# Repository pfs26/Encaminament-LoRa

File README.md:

# LoRa Static Routing Protocol for Monitoring Applications
This work presents the design and implementation of a modular and layered communication protocol based on LoRa and static routing, intended for monitoring device networks in extensive or isolated environments, where human presence is limited. The goal is to reduce the dependency on LoRaWAN gateways, taking advantage of the fact that devices are usually static and allow the use of predefined communication routes.

An application optimized for linear networks -a topology particularly useful in railway lines or tunnels- has been developed based on this protocol. It focuses on minimizing the energy consumption of the devices through a synchronization strategy between nodes, which allows coordinating transmissions and reducing the active time of the devices, without compromising reliability or the routing mechanisms provided by the protocol. The conducted tests have demonstrated that the proposed solution is viable, scalable, and efficient in environments where energy consumption and coverage are critical.

## Features
- **Custom LoRa MAC Protocol**
  - Layered protocol structure for modularity and easy extension
  - Unique node addressing and message relay
  - Static routing using **precomputed** routing tables, configurable during runtime
  - **CSMA** to avoid collisions, combined with **Binary Exponential Backoff (BEB)** if channel activity is detected
  - **Adaptive retransmission**, with dynamic transmission power adjustment
  - **TTL mechanism** to prevent routing loops
  - Simple **checksum-based error detection**
  - **Message deduplication** at the transport layer
  - **End-to-end acknowledgments** for reliable message delivery
  
- **LoRaWAN Relaying**
  - Nodes with LoRaWAN access can relay packets to the gateway
  - Handles end-to-end acknowledgment since LoRaWAN gateways cannot do this natively

- **Transport Layer**
  - Allows for optional end-to-end reliability
  - Segment deduplication 

- **Application Layer**
  - User-defined and fully customizable
  - Includes built-in low-power management, to be run on port `0x01`
  - Supports any logic needed, such as I2C sensor communication, dynamic configuration, etc.

## Repository Structure
```
├── firmware/          # ESP32 firmware for LoRa node
│   ├── src/           # LoRa protocol implementation
│   ├── include/       # Header files
│   ├── config/        # LoRa settings
├── tests/             # Tests and results, done during validation
├── memoria/           # Design and code documentation (.tex format)
└── README.md          # This file
```

## Protocol Architecture
The protocol is structured into multiple layers, each handling specific aspects of communication:

### LoRa Physical Layer
- Uses **SX1262 transceivers**
- Configurable modulation settings (SF, BW, TX power)

### MAC Layer
- **CSMA** with **Listen Before Talk (LBT)** to reduce collisions
- **Binary Exponential Backoff (BEB)** if the channel is busy

### Routing Layer
- **Static routing with runtime updates** via API (`RoutingTable_*()` functions)
- **TTL enforcement** to prevent looping packets
- Multiple LoRa interfaces support, for different configurations (raw LoRa vs LoRaWAN, or multiple raw LoRa transceivers)

### LoRaWAN Support
- Nodes with LoRaWAN access can forward packets to the gateway
- Uses LoRaWAN v1.1, using non-volatile storage to store nonces and keys
- OTAA for enhanced security
- Automatic LoRaWAN and raw LoRa mode swapping, storing connection information to avoid OTAA reactivations for each transmission 

### Transport Layer
- **Segment deduplication** using a unique **Segment ID**
- **End-to-end acknowledgment** ensures reliable delivery
- Automatic retransmissions if no acknowledgment is recevied, applying an exponential backoff after each attempt
- Unrealiable segments for quick end-to-end messaging

### Application Layer
- Customisable by the user, depending on requirements
- Uses the full protocol stack underneath
- **Built-in low-power** management application

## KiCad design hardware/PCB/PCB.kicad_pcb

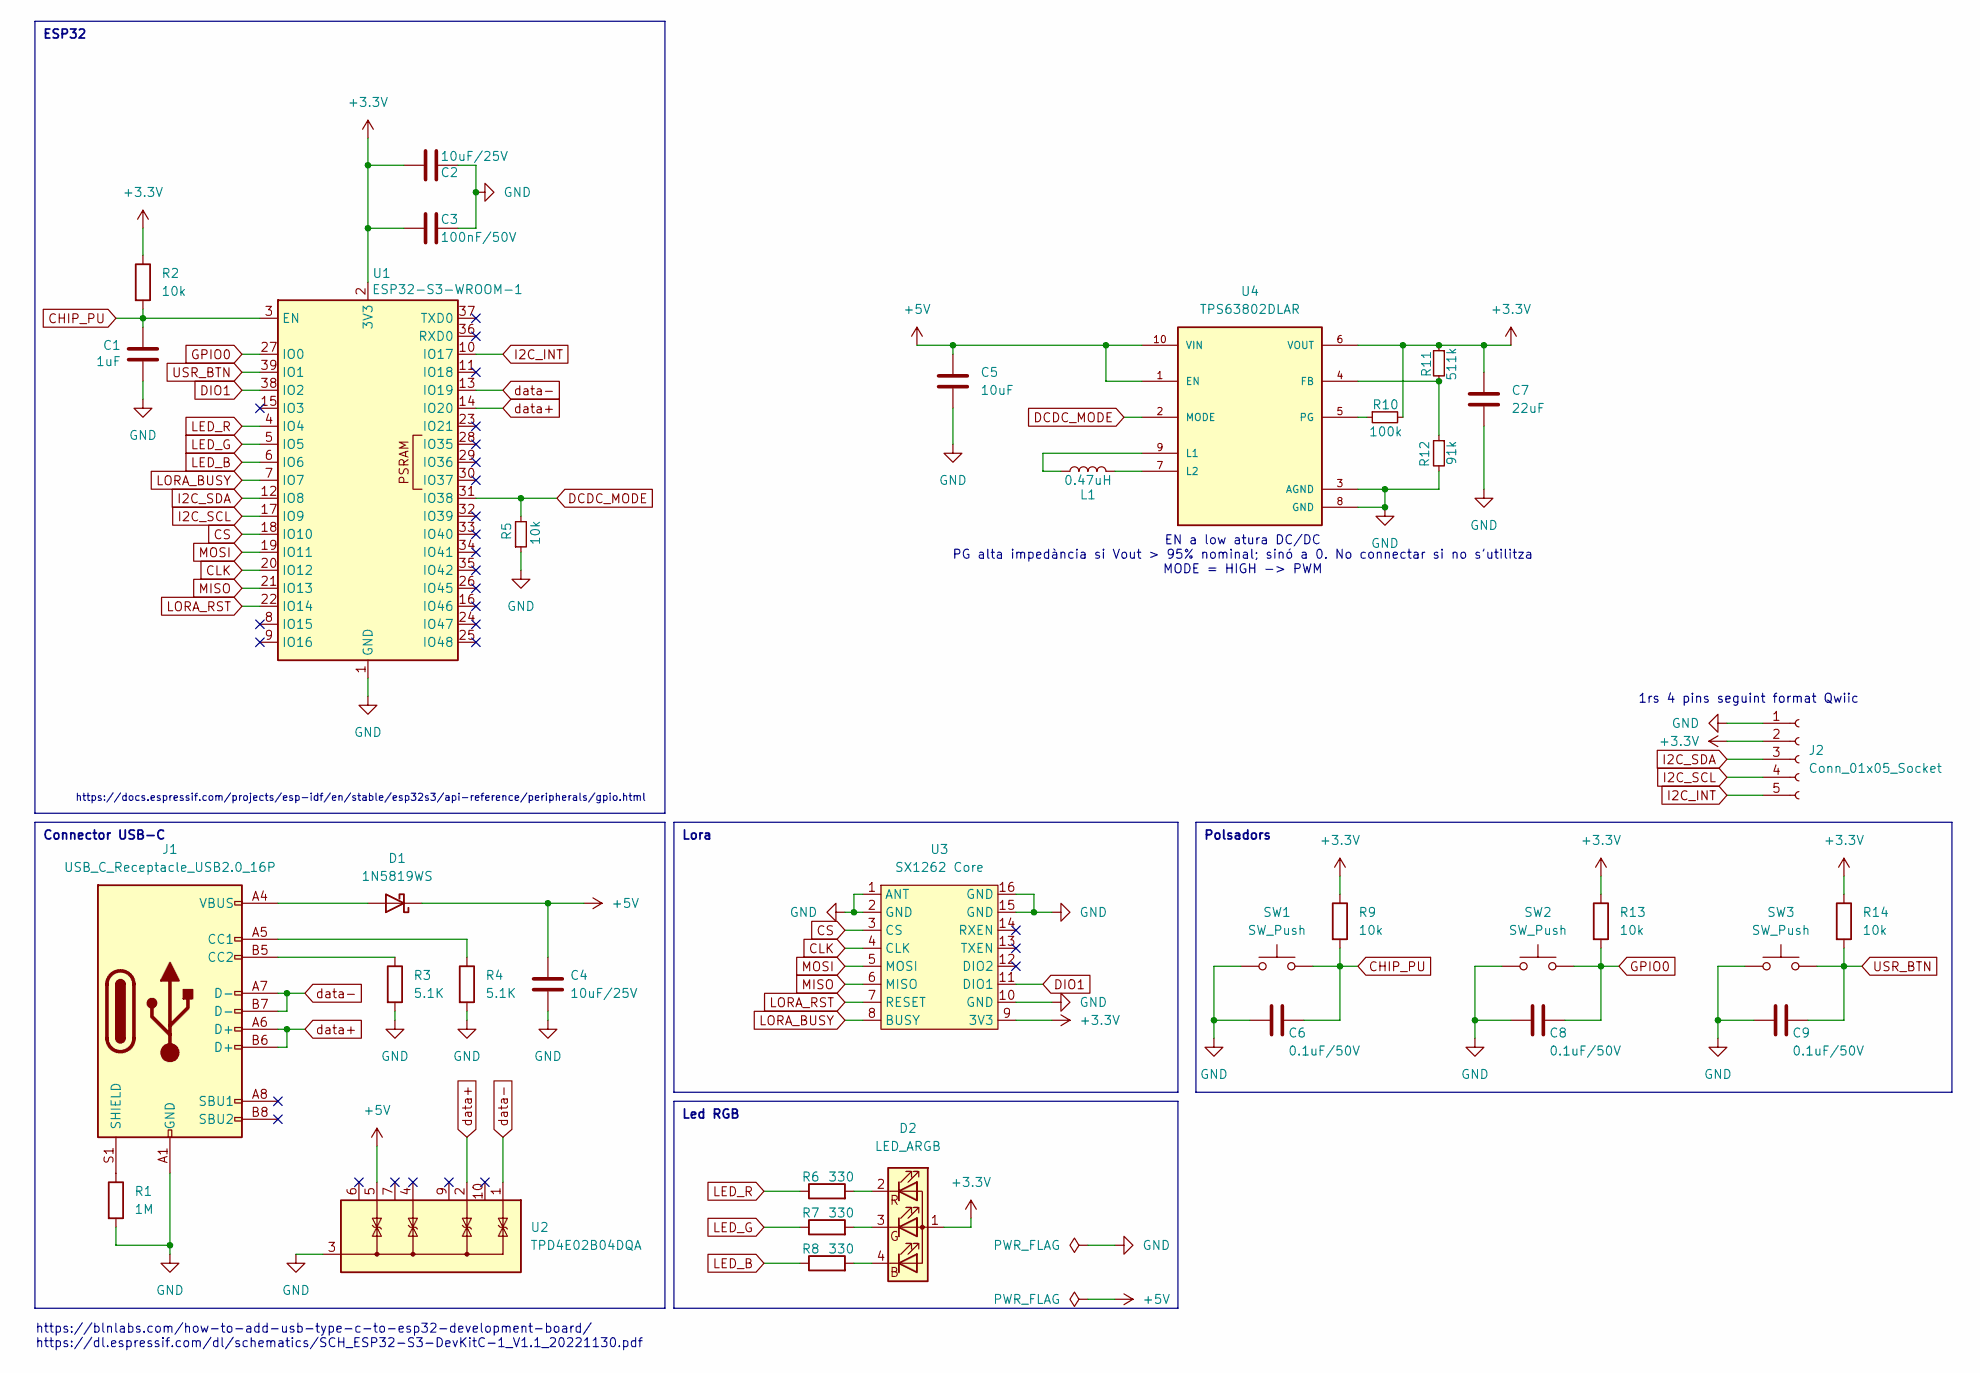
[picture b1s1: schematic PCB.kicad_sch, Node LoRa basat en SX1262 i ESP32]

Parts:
C1: 1uF; C_0805_2012Metric_Pad1.18x1.45mm_HandSolder
C2, C4: 10uF/25V; C_0805_2012Metric_Pad1.18x1.45mm_HandSolder
C3: 100nF/50V; C_0805_2012Metric_Pad1.18x1.45mm_HandSolder
C5: 10uF; C_0805_2012Metric_Pad1.18x1.45mm_HandSolder
C6, C8, C9: 0.1uF/50V; C_0805_2012Metric_Pad1.18x1.45mm_HandSolder
C7: 22uF; C_0805_2012Metric_Pad1.18x1.45mm_HandSolder
D1: 1N5819WS; D_SOD-323
D2: LED_ARGB; LED_RGB_Lumex_SML-LXT0805SIUGUBW
J1: USB_C_Receptacle_USB2.0_16P; USB_C_Receptacle_GCT_USB4085
J2: Conn_01x05_Socket; JST_PH_S5B-PH-K_1x05_P2.00mm_Horizontal
L1: 0.47uH; R_0805_2012Metric_Pad1.20x1.40mm_HandSolder
R1: 1M; R_0805_2012Metric_Pad1.20x1.40mm_HandSolder
R2, R5, R9, R13, R14: 10k; R_0805_2012Metric_Pad1.20x1.40mm_HandSolder
R3, R4: 5.1K; R_0805_2012Metric_Pad1.20x1.40mm_HandSolder
R6, R7, R8: 330; R_0805_2012Metric_Pad1.20x1.40mm_HandSolder
R10: 100k; R_0805_2012Metric_Pad1.20x1.40mm_HandSolder
R11: 511k; R_0805_2012Metric_Pad1.20x1.40mm_HandSolder
R12: 91k; R_0805_2012Metric_Pad1.20x1.40mm_HandSolder
SW1, SW2, SW3: SW_Push; SW_SPST_B3U-1000P
U1: ESP32-S3-WROOM-1
U2: TPD4E02B04DQA; USON-10_2.5x1.0mm_P0.5mm
U3: SX1262 Core
U4: TPS63802DLAR; VREG_TPS63802DLAR; PARTREV B

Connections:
+3.3V: C2.2, C3.2, C7.1, D2.1 (A), J2.2, R2.1, R9.1, R10.2, R11.1, R13.1, R14.1, U1.2 (3V3), U3.9 (3V3), U4.6 (VOUT)
+5V: C4.1, C5.1, D1.1 (K), U2.5 (IO4), U4.1 (EN), U4.10 (VIN)
CHIP_PU: C1.1, C6.1, R2.2, R9.2, SW1.2, U1.3 (EN)
CLK: U1.20 (IO12), U3.4 (CLK)
CS: U1.18 (IO10), U3.3 (CS)
DCDC_MODE: R5.2, U1.31 (IO38), U4.2 (MODE)
DIO1: U1.38 (IO2), U3.11 (DIO1)
GND: C1.2, C2.1, C3.1, C4.2, C5.2, C6.2, C7.2, C8.2, C9.2, J1.A1 (GND), J1.A12 (GND), J1.B1 (GND), J1.B12 (GND), J2.1, R1.2, R3.2, R4.2, R5.1, R12.2, SW1.1, SW2.1, SW3.1, U1.1 (GND), U1.40 (GND), U1.41 (GND), U2.3 (G), U2.8 (G), U3.1 (ANT), U3.2 (GND), U3.10 (GND), U3.15 (GND), U3.16 (GND), U4.3 (AGND), U4.8 (GND)
GPIO0: C8.1, R13.2, SW2.2, U1.27 (IO0)
I2C_INT: J2.5, U1.10 (IO17)
I2C_SCL: J2.4, U1.17 (IO9)
I2C_SDA: J2.3, U1.12 (IO8)
LED_B: R8.1, U1.6 (IO6)
LED_G: R7.1, U1.5 (IO5)
LED_R: R6.1, U1.4 (IO4)
LORA_BUSY: U1.7 (IO7), U3.8 (BUSY)
LORA_RST: U1.22 (IO14), U3.7 (RESET)
MISO: U1.21 (IO13), U3.6 (MISO)
MOSI: U1.19 (IO11), U3.5 (MOSI)
unnamed: D1.2 (A), J1.A4 (VBUS), J1.A9 (VBUS), J1.B4 (VBUS), J1.B9 (VBUS)
unnamed: D2.4 (BK), R8.2
unnamed: D2.3 (GK), R7.2
unnamed: D2.2 (RK), R6.2
unnamed: J1.A5 (CC1), R4.1
unnamed: J1.B5 (CC2), R3.1
unnamed: J1.S1 (SHIELD), R1.1
unnamed: R11.2, R12.1, U4.4 (FB)
unnamed: L1.1, U4.9 (L1)
unnamed: L1.2, U4.7 (L2)
unnamed: R10.1, U4.5 (PG)
USR_BTN: C9.1, R14.2, SW3.2, U1.39 (IO1)
data+: J1.A6 (D+), J1.B6 (D+), U1.14 (IO20), U2.2 (IO2)
data-: J1.A7 (D-), J1.B7 (D-), U1.13 (IO19), U2.1 (IO1)

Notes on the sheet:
Polsadors
Connector USB-C
ESP32
Led RGB
Lora
1rs 4 pins seguint format Qwiic
https://docs.espressif.com/projects/esp-idf/en/stable/esp32s3/api-reference/peripherals/gpio.html
https://blnlabs.com/how-to-add-usb-type-c-to-esp32-development-board/ https://dl.espressif.com/dl/schematics/SCH_ESP32-S3-DevKitC-1_V1.1_20221130.pdf
EN a low atura DC/DC PG alta impedància si Vout > 95% nominal; sinó a 0. No connectar si no s'utilitza MODE = HIGH -> PWM

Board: 2 copper layers, 35 parts (0 on the bottom side), 33 nets, no tracks yet.

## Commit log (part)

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2025-02-19 Repositori inicial. Fitxers inicials Node afegits (abstracció TaskScheduler)
2025-02-19 Fitxer exemple captive portal
2025-02-19 Mòdul gestor pàgina web per configuració inicial. Inicia portal capitiu (AP+DNS+WEB). Mètodes per iniciar i aturar
2025-02-21 Inici mòdul LoRa (físic) per interactuar amb RadioHead. S'utilitza scheduler per evitar bloquejar (com fa radiohead)
2025-02-21 DEV: Afegir funcions per obtenir SNR, RSSI, estat canal, modificar freq, i debug a mòdul LoRa
2025-02-26 DEBUG: Canviar llibreria lora a RadioLib per millor compatibilitat amb SX1262
2025-02-26 ERR: Error en interrupcions (WDT timeout). Fent backtrace sembla que prové de , que pot suposar un cost en temps gran
2025-02-27 DEBUG: Arreglar error interrupcions, utilitzant scheduler amb funció de gestió d'interrupcions. Closes #1
2025-02-27 DEV: Exemples i proves funcionament capa LoRa
2025-02-28 DEV: Nous macros debug afegits a utils.
2025-02-28 DEV: Afegir mètode per obtenir TimeOnAir a partir d'un nombre de bytes a LoRa
2025-03-01 DEBUG: Renombrar noms funcions privades lora per compatibilitat amb MAC
2025-03-01 DEV: Inici recepció. Mètode per convertir lora_data_t a mac_pdu_t i poder-hi tractar comodament
2025-03-01 DEV: Cont FSM Mac recepció. Debug mida dades enviades
2025-03-03 DEV: Classe de buffer circular per permetre cues de mida variable a les diferents capes (utilitzat de moment a capa MAC; en un futur a capa transport)
2025-03-04 DEBUG: Buffer circular hauria de ser de uint16_t i no de 8
2025-03-04 DEV: Mètode per enviar ACK a MAC. Error detecció ACK i en filtrat de recepció de missatges. Millores de format de debug
2025-03-04 DEBUG: Detalls a prints de debug per millor format
2025-03-04 DEV: Afegir linies debug a MAC. Proves TX RX. Bug detectat: en generar MAC TX ERR no es reben més interrupcions de LoRa
2025-03-05 ERR: Capa lora implementació amb multiinterrupcions sembla no ser l'adequada. Fi branca
2025-03-05 DEV: Canvis macros debug scheduler
2025-03-05 DEV: Refer capa LORA per utilitzar únicament interrupció en RX. Exemple amb dos TX afegit. Closes #2
2025-03-05 DEBUG: Si print dins de scheduler reset per timer de WDT. Eliminar
2025-03-05 canvi config no crític
2025-03-05 DEV: Primera refactorització capa MAC. Eliminar atribut length de PDU (ja que tampoc existeix com a tal a la transmissió). Utilitza '\0' com a final en tots els casos. Càlcul de CRC refet per utilitz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
2025-03-05 DEV: Incloure datalength a header de MAC. No es pot utilitzar \0 -> Fallaria si capa superior té un byte 0x00 entre mig de les dades
2025-03-05 DEV: Afegir mètode per forçar inici de recepció de LoRa. Evita que es quedi en mode standby quan hi ha un MAC tx err
2025-03-06 DEV: Millores a traces de debug per mostrar colors més intuitius
2025-03-06 Dev: continuació reimplementació FSM mac
2025-03-06 feat: millores a macros debug per aliniar text
2025-03-06 Debug: arreglar error lectura dades MAC des de capa superior. Closes #3
2025-03-07 Debug: evitar callbacks de LoRa a MAC després de deinicialitzar LoRa
2025-03-07 feat: afegir valors estadístics a capa MAC (errorsTX, errorsCRC, recepcions, enviaments correctes)
2025-03-07 refactor: canviar declaració MAC PDU per utilitzar directament mac_data_t i no redefinir un array de nou
2025-03-07 dev: implementació inicial taula de rutes a NVS i la seva gestió
2025-03-07 feat: primeres implementacions capa encaminament.
2025-03-08 fix: arreglar error si taula rutes mai creada generava inicialització fallida
2025-03-08 debug: canviar format adreces a capa MAC per utilitzar hex
2025-03-09 feat: inici implementació FSM per permetre buffers de transmissió, amb 2 prioritats per ACK i data. S'observa com potser és millor utilitzar ACKs explícits, per evitar barrejar tasques de capes (rout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
2025-03-10 feat: afegir mètode per obtenir mida de LinkedFIFO
2025-03-10 debug: en proves amb canal ocupat fictici, BEB no inicia recepció lora; arreglat forçant recepció lora enc as de chan busy
2025-03-11 feat: tenir en compte regulacions de duty cycle en enviar per LoRa. Potser no és el més lògic aplicar-ho si s'ha d'enviar un ACK; veure què es pot fer (potser tenir en compte el temps transcorregut a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
2025-03-12 feat: afegir mètodes per obtenir mides de buffers de MAC
2025-03-12 feat: mètode per obtenir missatges pendents de ser rebuts a capa MAC. Es dona per acabada les cues. Closes #4
2025-03-12 feat: primera iteració mòdul LoRaWAN. Falta verificar en un gateway. Hi pot haver conflictes entre LoRaWAN i LoRa pelat -> mirar de deshabilitat interrupcions generades per sx1262 quan s'interactua a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
2025-03-13 refactor: utilitzar node_address a routingTable
2025-03-14 feat: macro per imprimir arrays a consola en ascii i hex, per debug
2025-03-14 feat: implementar capa LoRa, modificar LoRa existent a LoRaRAW per afegir capa d'abstracció clara sobre radio, i permetre sincronització entre RAW i WAN
2025-03-14 debug: mala inicialització de nou modul lora a mac
2025-03-14 debug: error en validació d'adreça de node correcte a macro
2025-03-16 feat: afegir propagació ID a routing_send
2025-03-17 feat: implementació capa transport utilitzant propagació d'ID de MAC, enviar segments amb o sense reconeixement, rebre segments i enviar ACK si sol·licitat
2025-03-18 comments: comentaris a codi no importants
2025-03-21 feat: implementar potència de transmissió adaptativa en funció de reintents
2025-03-21 docu: comentaris bàsics i canvis de defines a lora
2025-03-21 feat: implementari lògica routing per enviar cap a lorawan si som gateway
2025-03-21 readme update
2025-03-24 feat: més versions de PCB i layouts inicials
2025-03-25 debug: comprovació timeout ack transport. Comentari important a routing referent a #8
2025-03-25 refactor: canviar nom d'adreça de gateway per mantenir coherència amb altres adreces
2025-03-26 debug: limitar potència màxima per evitar crash d'esp per falta de corrent
2025-03-26 debug: canviar missatge de debug per ser més informatiu
2025-03-26 feat: prova comentada si s'envia paquet a un mateix
2025-03-26 feat: implementar configuració de callbacks depenent de port per millor gestió a capa aplicació. Closes #11. Gestió de múltiples inicialitzacions i deinicialitzacions a capa aplicació (que hauria de 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
2025-03-27 feat: implementar guardar nonces a NVS per complir amb especificació v1.1 de LoRaWAN. Closes #14
2025-03-28 debug: aplicar logica preprocessador per si no es defineix duty cycle. De moment no acaba d'estar ben implementat restriccions de duty cycle
2025-03-29 debug: error en obtenir nonces de nvs a lorawan
2025-04-01 feat: implementar lloc central per configurar node, i mètodes per guardar/obtenir configuracions dinàmiques per UI
2025-04-01 feat: implementació capa aplicació per a baix consum
2025-04-04 feat: plantilla inicial latex per memòria. índex v1
2025-04-04 debug: error en comprovar si un port ja s'estava utilitzant a transport
2025-04-04 debug: eliminar assignació inicial nodes a reenviar
2025-04-07 feat: implementar missatges debug a sleep, i conversions més fàcilmetn
2025-04-08 debug: si un node és iniciador de sleep sync no s'hauria de modificar el sue cicle de sleep
2025-04-08 debug: a sleep s'executava abans que enviament de SYNC
2025-04-08 debug: permetre rebre ACK i dades a la vegada a transport
2025-04-08 debug: flag ackResponse no es definia a 0 en generar un segment, podent prendre qualsevol valor
2025-04-08 debug: random a capa mac no inclou valor màxim. Paràmetre temps de guardia a sleep
2025-04-08 memoria: comentaris i canvis a index
2025-04-09 memoria: canvis a TOC
2025-04-13 memoria: acabar apartat protocols
2025-04-14 memoria: acabar lora + lorawan
2025-04-15 memoria: inici disseny protocol
2025-04-16 memoria: imatge diagrama
2025-04-18 debug: ACK MAC té destí ben definit; ID igual a ID a reconeixer. Closes #15
2025-04-18 memoria: afegir dos diagrames de situacions de capa mac
2025-04-19 memoria: diagrama situacio especial accés al medi. LoRaWAN. Cues recepció
2025-04-20 memoria: mac diagrama complet
2025-04-22 memoria: implementacio routing + diagrames
2025-04-24 memoria: diagrama TX transport amb errors
2025-04-25 debug: erro calcul tout onsend segment. Closes #19
2025-04-25 feat: potència de transmissió d'ACK de capa MAC depèn del nombre de reintents realitzats per la transmissió del frame rebut. Closes #16
2025-04-25 feat: afegir notificacions de txerror. Permetre notificacions de tx i txerror també per UDP. Metadades ara globals i no únicament per TCP
2025-04-25 test: verificacio canvis transport
2025-04-27 memoria: explicar notificacions txerror. Explicar criteris establir K fiabilitat transport
2025-04-29 memoria: diagrama encaminament bàsic. Falta comentar-lo
2025-05-01 memoria: error en una paraula
2025-05-03 feat: implementar capa sleep amb nou algoritme
2025-05-03 resultat: proves resultats capa APP. Sense simular reintents, i inici ismulant
2025-05-05 feat: millorar tout ack, aplicant únicament el temps de transmetre les dades d'un ACK i no múltiples
2025-05-05 memoria: explicar estructura codi i comunicació; diagrama capes
2025-05-05 feat: implementar càlcul temps delta de forma dinàmica a partir de nodes anteriors. Calcular despres de rebre ja que s'ha fet calcul de nou de nodes i pot afectar temps sleep
2025-05-06 exemples: test bàsci lora millorat, millora verificació max length
2025-05-06 debug: error en ppm de clock rtc. Per proves sense rtc extern, millor utilitzar 8000. No es considerava error de clock del dispositiu anterior
2025-05-06 memoria: seccio verificació inicial. Exemples MAC ben definits
2025-05-08 Resultats: afegir resultats 2
2025-05-12 memoria: situacio baix consum i limitacions
2025-05-13 memoria: sinc explicita
2025-05-15 diagrama opcio sync explicita 1 i 2 vàlids?
2025-05-15 diagrama 2 millorat. Comentaris diagrama dos i altres opcions
2025-05-16 memoria: començar a explicar sincronització amb dades acumulades
2025-05-18 memoria: diagrama sync dades partides estategia 1 BO SI US PLAU AUQEST ES BO!
2025-05-19 memoria: diagrama sync 2 acumulat
2025-05-19 memoria: revisio text escrit sync acum
2025-05-21 debug: error en rebre lora d'altra gent amb mides inferiors a mínima i mal format de trames
2025-05-21 debug: eliminar correció clock sleep. Valors per defecte sleep i unitats uint64t correctes en float
2025-05-21 memoria: situacions no ideals sync final
2025-05-21 memoria: diagrama error retrnamissio calcul delta
2025-05-22 memoria: explicat limit de dades i fragmentacio
2025-05-23 memoria: afegir timeout a solució final
2025-05-24 memoria: no sé ni que he fet
2025-05-25 feat: callback sleep proporciona la mida de les dades que ha de copiar
2025-05-25 memoria: revisió i utilització app. Fer que numero dispositius sigui definició i no variable
2025-05-27 estructura: canviar estructura carpetes pensant en entrga final
2025-05-28 memoria: errors en proves
2025-05-28 memoria: ref system time esp32
2025-05-28 tests: fitxer python analisis logs. Logs 1 minut amb tout
2025-05-28 exemples: exemple capa sleep
2025-05-28 refactor: eliminar codi comentar de lora.cpp
2025-05-28 update platformio
2025-05-28 refactor: eliminar resultats que no aporten res, i no cal entregar.
2025-05-28 eliminar tests innecessaris
2025-05-29 memoria: introducció revisada
2025-05-29 test 1min tout. Eliminar bytes invàlids afegits per picocom de logs
2025-05-29 analisis amb millor format. Arreglar fitxer log listener
2025-05-29 imatges analisi i plaques per proves
2025-05-31 memoria: afegir conclusions i revisar-les
2025-06-01 memoria: fsm mac
2025-06-01 revisió abstract i introducció
2025-06-01 faltes lora/lorawan
2025-06-01 faltes treballs relaciontats
2025-06-01 faltes capa física
2025-06-01 faltes capa encaminament
2025-06-01 faltes aplicació i validacions protocol
2025-06-01 faltes aplicació: dissenys inicials
2025-06-01 faltes conclusions i treball futur
2025-06-03 moure config sleep a config-h
2025-06-04 codi: comentaris config
2025-06-04 eliminar readme lib
2025-06-04 codi: retornar adreça recepció segment a transport
2025-06-04 comentari lora
2025-06-04 codi: fer static lorawan
2025-06-04 comentaris capa mac
2025-06-04 static i documentacio capa encaminament
2025-06-04 static i documentacio transport
2025-06-06 correcions memoria finals
